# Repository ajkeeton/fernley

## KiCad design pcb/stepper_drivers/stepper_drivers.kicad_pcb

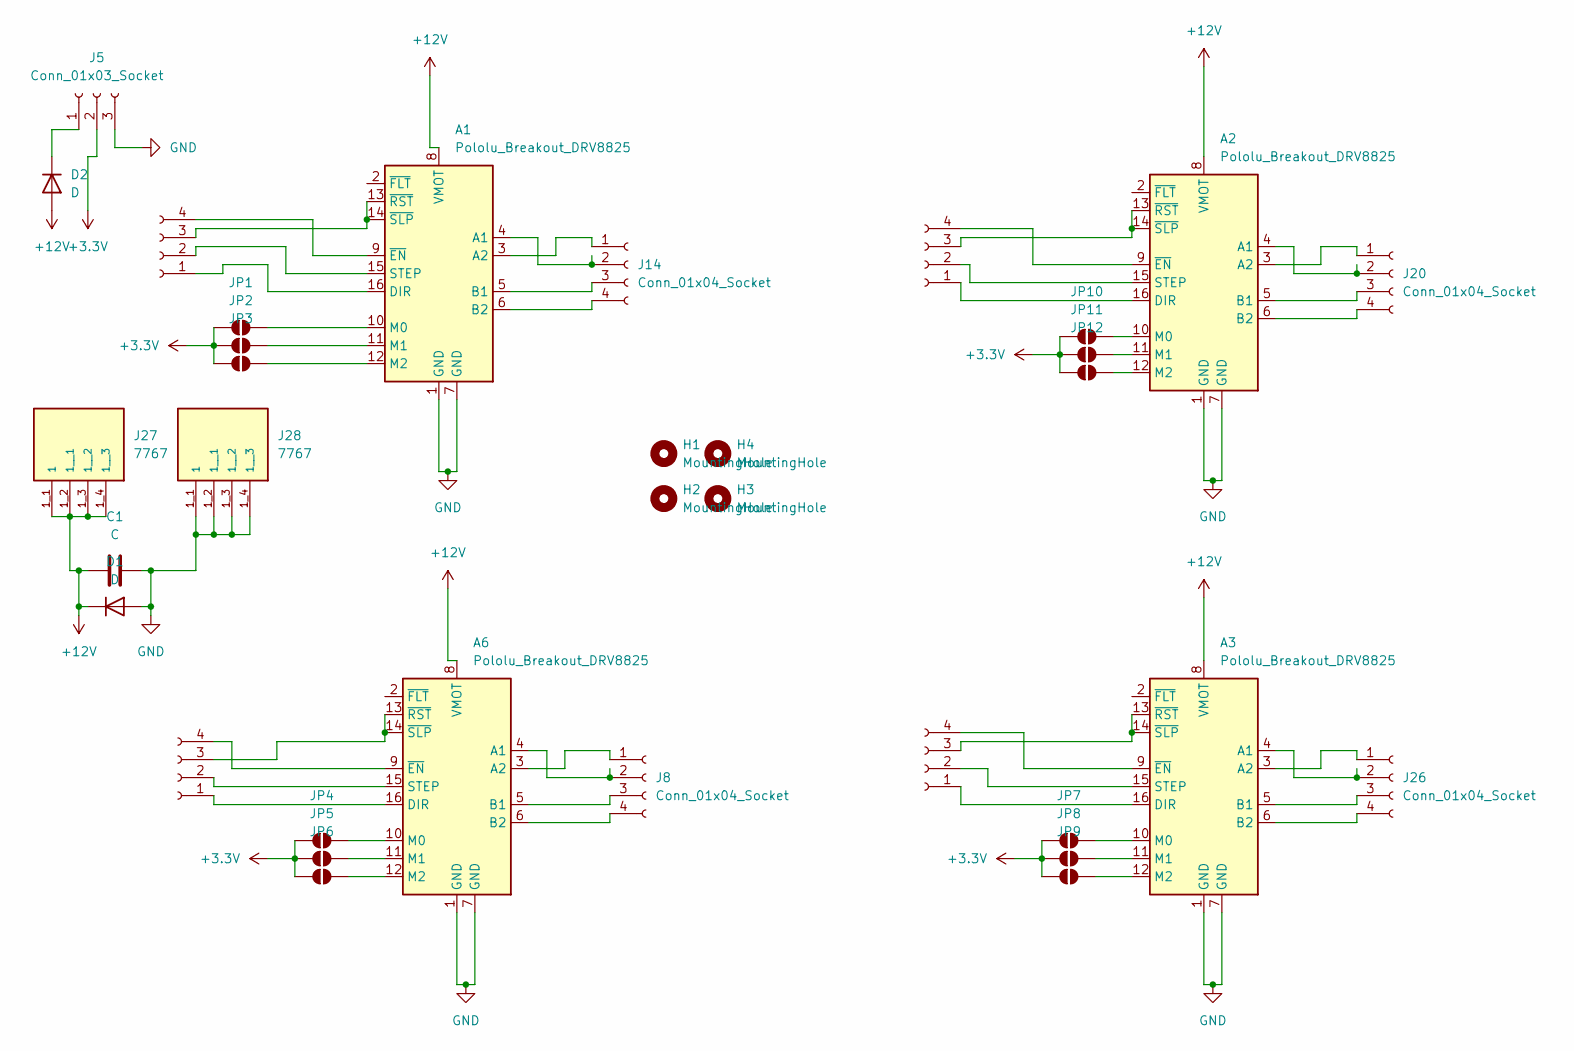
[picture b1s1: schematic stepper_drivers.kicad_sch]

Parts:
A1, A2, A3, A6: Pololu_Breakout_DRV8825; Pololu_Breakout-16_15.2x20.3mm
C1: C; CP_Radial_D13.0mm_P5.00mm
D1: D; D_A-405_P5.08mm_Vertical_AnodeUp
D2: D; D_DO-27_P15.24mm_Horizontal
H1, H2, H3, H4: MountingHole; MountingHole_2.5mm_Pad_TopBottom
J1, J2, J3, J4, J8, J14, J20, J26: Conn_01x04_Socket; PinHeader_1x04_P2.54mm_Vertical
J5: Conn_01x03_Socket; PinHeader_1x03_P2.54mm_Vertical
J27, J28: 7767; KEYSTONE_7767; PARTREV B
JP1, JP2, JP3, JP4, JP5, JP6, JP7, JP8, JP9, JP10, JP11, JP12: SolderJumper_2_Open; SolderJumper-2_P1.3mm_Open_Pad1.0x1.5mm

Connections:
+3.3V: J5.2, JP1.1 (A), JP2.1 (A), JP3.1 (A), JP4.1 (A), JP5.1 (A), JP6.1 (A), JP7.1 (A), JP8.1 (A), JP9.1 (A), JP10.1 (A), JP11.1 (A), JP12.1 (A)
+12V: A1.8 (VMOT), A2.8 (VMOT), A3.8 (VMOT), A6.8 (VMOT), C1.1, D1.1 (K), D2.2 (A), J27.1_1 (1), J27.1_2 (1__1), J27.1_3 (1__2), J27.1_4 (1__3)
GND: A1.1 (GND), A1.7 (GND), A2.1 (GND), A2.7 (GND), A3.1 (GND), A3.7 (GND), A6.1 (GND), A6.7 (GND), C1.2, D1.2 (A), J5.3, J28.1_1 (1), J28.1_2 (1__1), J28.1_3 (1__2), J28.1_4 (1__3)
unnamed: A1.4 (A1), J14.2
unnamed: A1.3 (A2), J14.1
unnamed: A1.5 (B1), J14.3
unnamed: A1.6 (B2), J14.4
unnamed: A1.16 (DIR), J2.1
unnamed: A1.10 (M0), JP1.2 (B)
unnamed: A1.11 (M1), JP2.2 (B)
unnamed: A1.12 (M2), JP3.2 (B)
unnamed: A1.15 (STEP), J2.2
unnamed: A1.9 (~EN), J2.4
unnamed: A1.13 (~RST), A1.14 (~SLP), J2.3
unnamed: A2.4 (A1), J20.2
unnamed: A2.3 (A2), J20.1
unnamed: A2.5 (B1), J20.3
unnamed: A2.6 (B2), J20.4
unnamed: A2.16 (DIR), J3.1
unnamed: A2.10 (M0), JP10.2 (B)
unnamed: A2.11 (M1), JP11.2 (B)
unnamed: A2.12 (M2), JP12.2 (B)
unnamed: A2.15 (STEP), J3.2
unnamed: A2.9 (~EN), J3.4
unnamed: A2.13 (~RST), A2.14 (~SLP), J3.3
unnamed: A3.4 (A1), J26.2
unnamed: A3.3 (A2), J26.1
unnamed: A3.5 (B1), J26.3
unnamed: A3.6 (B2), J26.4
unnamed: A3.16 (DIR), J4.1
unnamed: A3.10 (M0), JP7.2 (B)
unnamed: A3.11 (M1), JP8.2 (B)
unnamed: A3.12 (M2), JP9.2 (B)
unnamed: A3.15 (STEP), J4.2
unnamed: A3.9 (~EN), J4.4
unnamed: A3.13 (~RST), A3.14 (~SLP), J4.3
unnamed: A6.4 (A1), J8.2
unnamed: A6.3 (A2), J8.1
unnamed: A6.5 (B1), J8.3
unnamed: A6.6 (B2), J8.4
unnamed: A6.16 (DIR), J1.1
unnamed: A6.10 (M0), JP4.2 (B)
unnamed: A6.11 (M1), JP5.2 (B)
unnamed: A6.12 (M2), JP6.2 (B)
unnamed: A6.15 (STEP), J1.2
unnamed: A6.9 (~EN), J1.4
unnamed: A6.13 (~RST), A6.14 (~SLP), J1.3
unnamed: D2.1 (K), J5.1

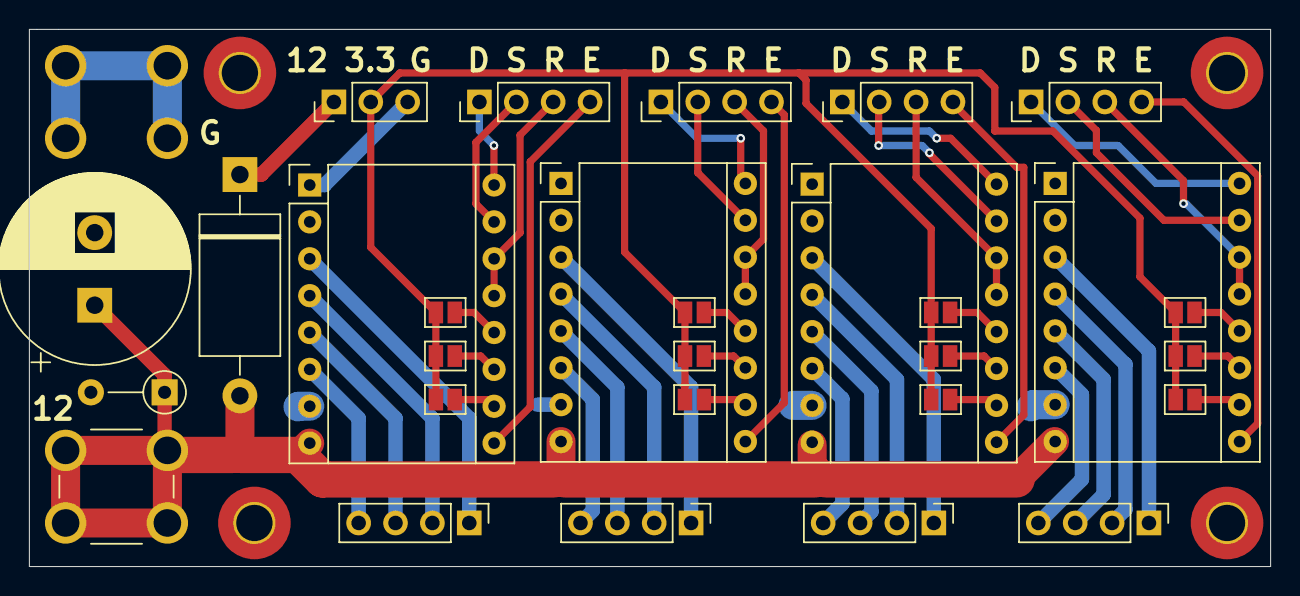
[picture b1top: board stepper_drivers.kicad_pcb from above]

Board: 2 copper layers, 85.5 x 37.0 mm, 34 parts (1 on the bottom side), 48 nets.

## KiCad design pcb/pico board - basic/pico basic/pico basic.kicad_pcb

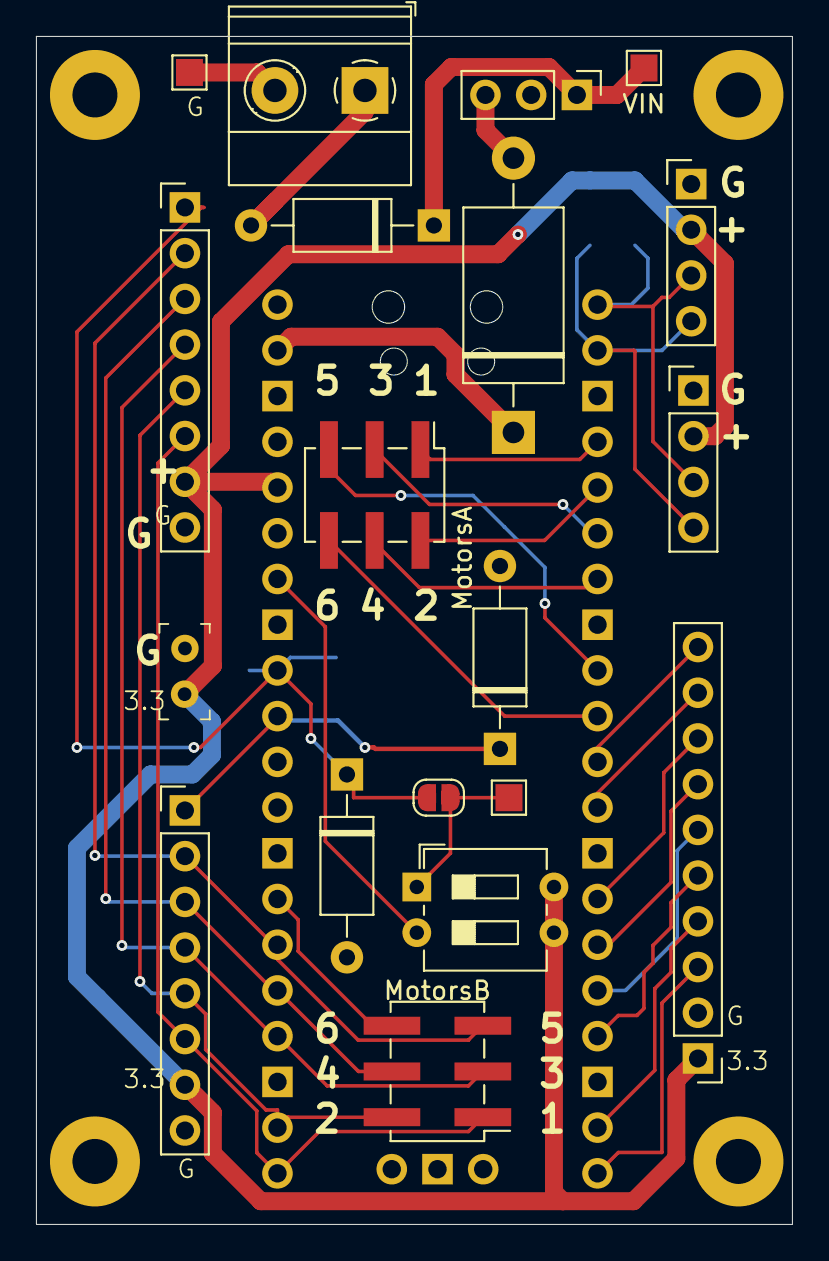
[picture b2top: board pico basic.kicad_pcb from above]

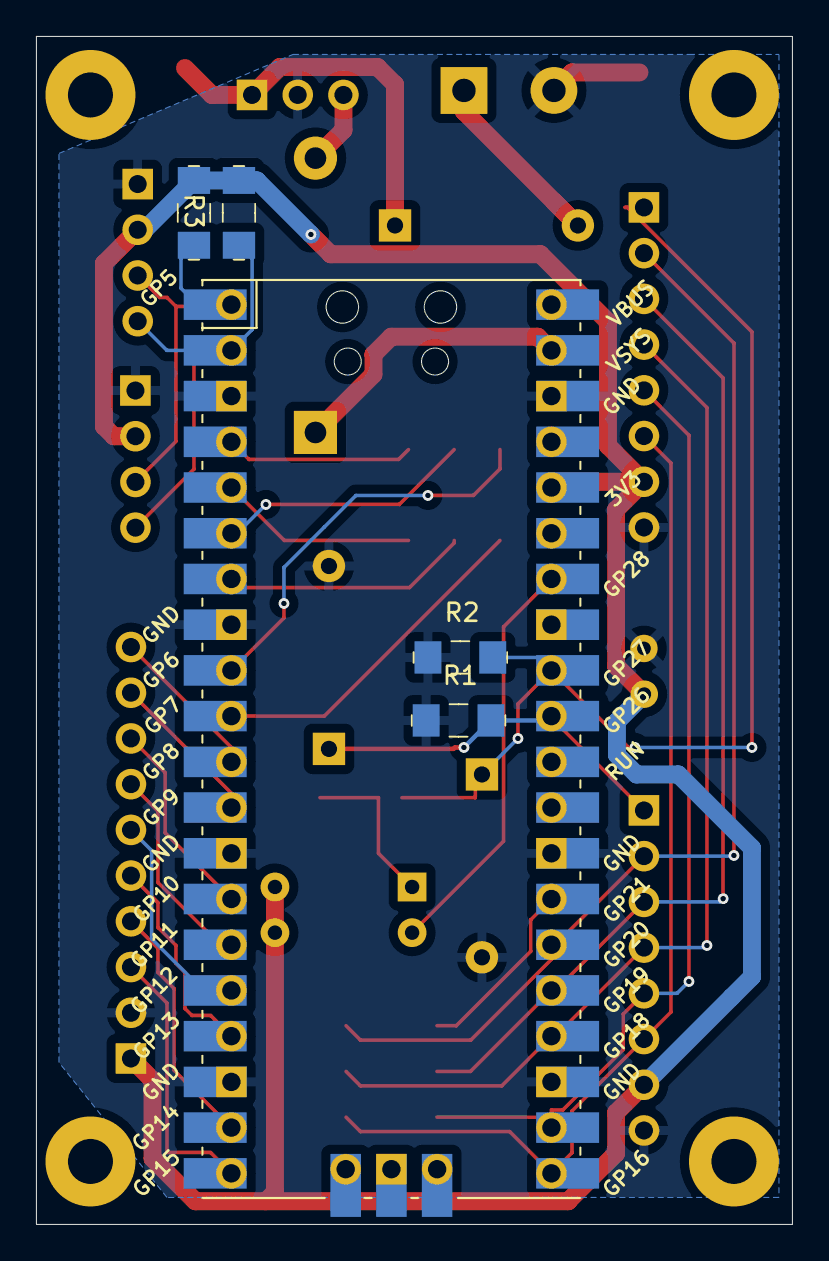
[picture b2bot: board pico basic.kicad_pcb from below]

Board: 2 copper layers, 42.0 x 66.0 mm, 28 parts (5 on the bottom side), 32 nets.

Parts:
D1: D_Schottky; D_DO-27_P15.24mm_Horizontal
D2, D3, D4: D; D_A-405_P10.16mm_Horizontal
GND2: TestPoint; TestPoint_Pad_1.5x1.5mm
H1, H2, H3, H4: MountingHole; MountingHole_2.5mm_Pad
I2C1, I2C2: Conn_01x04_Pin; PinHeader_1x04_P2.54mm_Vertical
J1: Conn_01x10_Socket; PinHeader_1x10_P2.54mm_Vertical
J2, J3: Conn_01x08_Socket; PinHeader_1x08_P2.54mm_Vertical
J4: Conn_01x02_Socket; PinHeader_1x2_P2.54mm
JP1: SolderJumper_2_Open; SolderJumper-2_P1.3mm_Open_RoundedPad1.0x1.5mm
MotorsA: Conn_01x06_Pin; PinHeader_2x03_P2.54mm_Vertical_SMD
MotorsB: Conn_01x06_Pin; PinHeader_2x03_P2.54mm_Vertical_SMD
R1, R2, R3, R4: R; 1206
SW1: TestPoint; TestPoint_Pad_1.5x1.5mm
SW2: SW_DIP_x02; SW_DIP_SPSTx02_Slide_6.7x6.64mm_W7.62mm_P2.54mm_LowProfile
U1: Pico; RPi_Pico_SMD_TH
VIN: TestPoint; TestPoint_Pad_1.5x1.5mm
VReg1: Conn_01x03_Pin; PinHeader_1x03_P2.54mm_Vertical
Vin1: Screw_Terminal_01x02; TerminalBlock_Phoenix_MKDS-1,5-2_1x02_P5.00mm_Horizontal

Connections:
+3.3V: I2C1.2, I2C2.2, J1.1, J2.7, J3.7, J4.1, R3.2, R4.1, SW2.3, SW2.4, U1.36 (3V3)
+5V: D1.2 (A), VReg1.3
GND: D3.2 (A), D4.2 (A), GND2.1, I2C1.1, I2C2.1, J1.2, J2.8, J3.8, J4.2, R1.1, R2.1, U1.3 (GND), U1.8 (GND), U1.13 (GND), U1.18 (GND), U1.23 (GND), U1.28 (GND), U1.38 (GND), VReg1.2, Vin1.2
unnamed: D1.1 (K), U1.39 (VSYS)
unnamed: D2.2 (A), Vin1.1
unnamed: D2.1 (K), VIN.1, VReg1.1
unnamed: D3.1 (K), J3.1, JP1.2 (B), R2.2, U1.32 (GPIO27_ADC1)
unnamed: D4.1 (K), J2.1, R1.2, U1.31 (GPIO26_ADC0)
unnamed: I2C1.3, I2C2.3, R4.2, U1.1 (GPIO0)
unnamed: I2C1.4, I2C2.4, R3.1, U1.2 (GPIO1)
unnamed: J1.3, U1.20 (GPIO15)
unnamed: J1.4, U1.19 (GPIO14)
unnamed: J1.5, U1.17 (GPIO13)
unnamed: J1.6, U1.16 (GPIO12)
unnamed: J1.7, U1.15 (GPIO11)
unnamed: J1.8, U1.14 (GPIO10)
unnamed: J1.9, U1.12 (GPIO9)
unnamed: J1.10, U1.11 (GPIO8)
unnamed: J2.2, J3.2, MotorsB.5, U1.26 (GPIO20)
unnamed: J2.3, J3.3, MotorsB.4, U1.25 (GPIO19)
unnamed: J2.4, J3.4, MotorsB.3, U1.24 (GPIO18)
unnamed: J2.5, J3.5, MotorsB.2, U1.22 (GPIO17)
unnamed: J2.6, J3.6, MotorsB.1, U1.21 (GPIO16)
unnamed: JP1.1 (A), SW1.1, SW2.1
unnamed: MotorsA.1, U1.4 (GPIO2)
unnamed: MotorsA.2, U1.5 (GPIO3)
unnamed: MotorsA.3, U1.6 (GPIO4)
unnamed: MotorsA.4, U1.7 (GPIO5)
unnamed: MotorsA.5, U1.9 (GPIO6)
unnamed: MotorsA.6, U1.10 (GPIO7)
unnamed: MotorsB.6, U1.27 (GPIO21)
unnamed: SW2.2, U1.34 (GPIO28_ADC2)

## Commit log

2024-11-20 je_spiral initial steps
2024-12-01 New hinge segments
2024-12-01 Adding initial work for linkages
2025-01-10 Adding latest control pcb
2025-01-12 New test/PoC code and models
2025-02-01 Models and test code
